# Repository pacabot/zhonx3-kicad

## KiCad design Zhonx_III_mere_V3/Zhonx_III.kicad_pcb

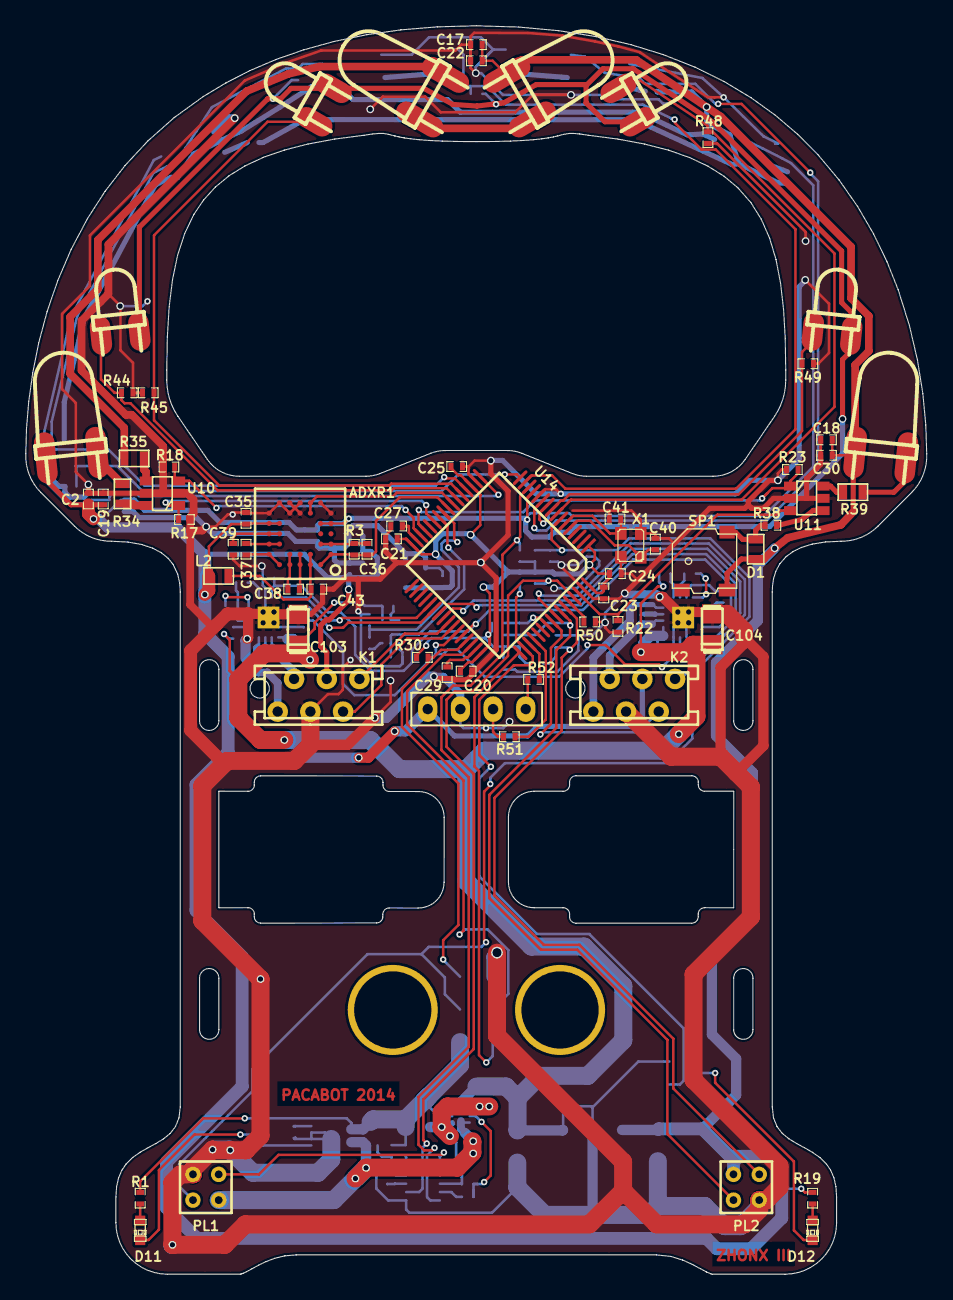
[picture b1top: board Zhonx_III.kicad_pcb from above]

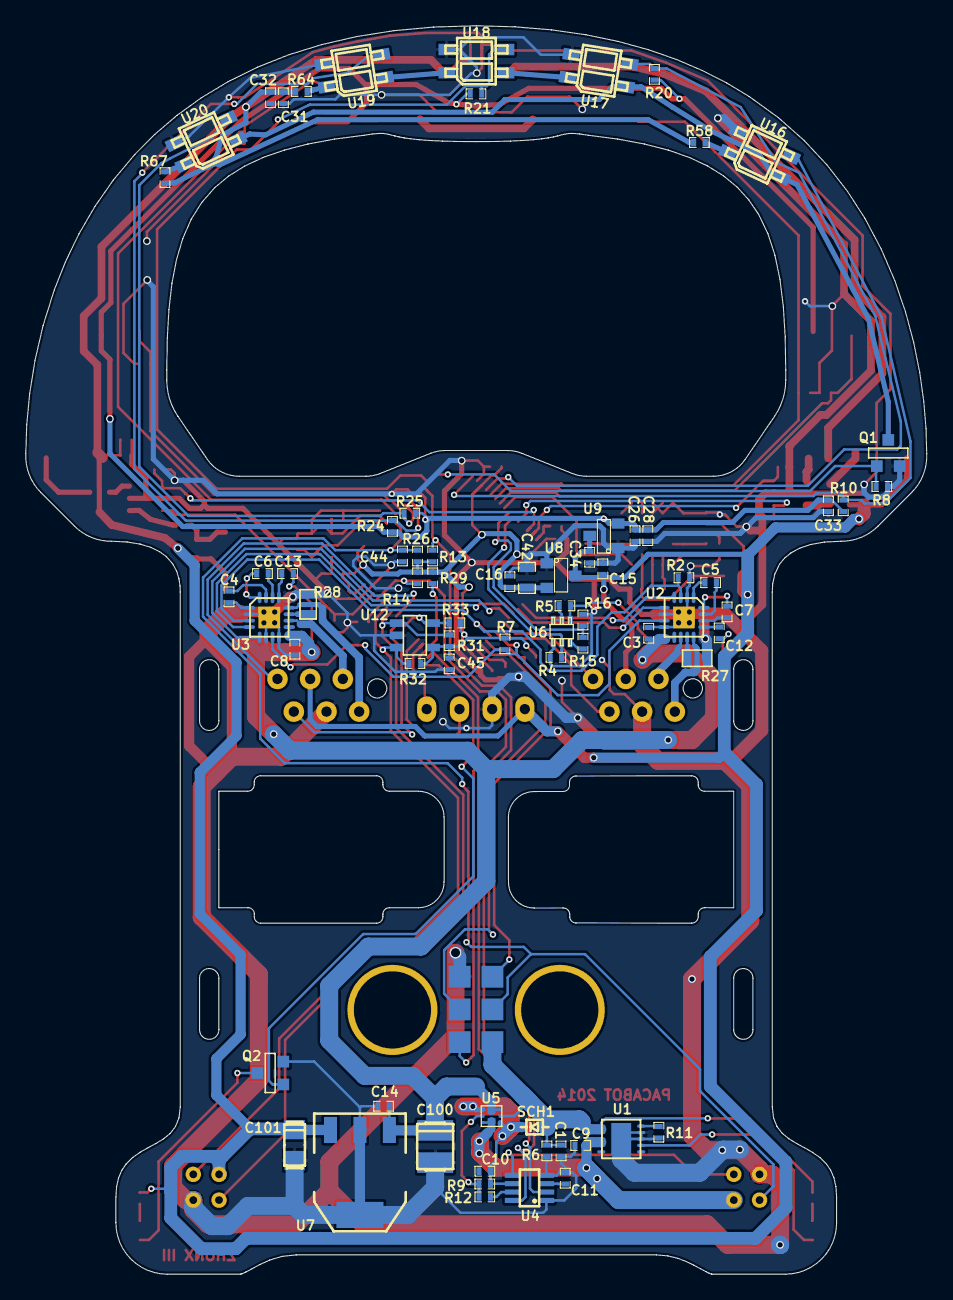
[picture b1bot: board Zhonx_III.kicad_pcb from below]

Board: 2 copper layers, 70.0 x 97.0 mm, 133 parts (73 on the bottom side), 104 nets.

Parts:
ADXR1: ADXRS620
C1, C9, C27, C29: 2,2uF; SM0402_ZHONX
C2, C17, C18, C20, C31: 4,7uF; SM0402_ZHONX
C3, C4, C5, C6, C7, C8, C10, C12, C13, C14, C15, C16, C19, C21, C22, C23, C24, C25, C30, C32, C33, C35, C39, C43, C44, C45: 0,1uF; SM0402_ZHONX
C11: 150nF; SM0402_ZHONX
C26, C34: 1uF; SM0402_ZHONX
C28: 10nF; SM0402_ZHONX
C36, C37, C38: 22nF; SM0402_ZHONX
C40, C41: 18pF; SM0402_ZHONX
C42: 10uF; SM0603_Capa
C100: 100uF; SM1210_Capa
C101, C103, C104: 100uF; SM1206_Capa
D1: 4148; SM0603
D11: Bleue; LED-0603
D12: Blanc; LED-0603
IR1: L_Front; IR_LF
IR2: L_Diag; IR_LD
IR3: R_Diag; IR_RD
IR4: R_Front; IR_RF
K1: L_Motor; Connecteur_Moteur_Zhonx
K2: R_Motor; Connecteur_Moteur_Zhonx
K3: USART; Conn_Serial_Zhonx
L2: 10uH; SM0603
P1: JTAG; Zhonx_III_JTAG
PL1: PLATINE_ZHONX_III; Platine_Zhonx_III
Q1, Q2: FDV301N; SOT23GDS
R1: 3,3K; SM0402_ZHONX
R2, R7, R8, R10, R13, R14, R17, R18, R20, R21, R22, R23, R24, R25, R29, R30, R33: 47K; SM0402_ZHONX
R3: 90K; SM0402_ZHONX
R4, R5: 1M; SM0402_ZHONX
R6, R9, R12, R26, R50: 100K; SM0402_ZHONX
R11, R16: 10K; SM0402_ZHONX
R15: 20K; SM0402_ZHONX
R19: 820; SM0402_ZHONX
R27, R28: 0,2; SM0603_ZHONX
R31, R32: 4,7K; SM0402_ZHONX
R34, R39: 12; SM0603_ZHONX
R35: 2,8; SM0603_ZHONX
R38: 100; SM0402_ZHONX
R44, R45, R48, R49: 1,8K; SM0402_ZHONX
R51, R52: 510; SM0402_ZHONX
R58, R67: 220; SM0402_ZHONX
R64: 33; SM0402_ZHONX
SCH1: BAT60; SOD323
SP1: KSSG13J12; Buzzer_KSSG13J12
U1: MCP73213
U2, U3: A3918; QFN16_Termal_Pad
U4: LTC2955CTS8-2; LTC2955
U5: SIB911DK; SC75-6L
U6: SI1551DL; SC70
U7: LM2940; SOT223
U8, U9: MCP1700; SOT23
U10, U11: BSL214N; SOT23_6
U12: 24LC64T; SOT23-5
U14: STM32F405RGT6; TQFP_64
U16: Line_1; QRE1113GR
U17: Line_2; QRE1113GR
U18: Line_3; QRE1113GR
U19: Line_4; QRE1113GR
U20: Line_5; QRE1113GR
X1: 16MHz; Quartz_8Z-16MHz

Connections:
+3.3V: C16.1, C20.2, C21.2, C23.2, C24.2, C25.2, C42.1, C45.1, R7.1, R13.2, R14.2, R26.1, R29.2, R30.1, R31.2, R32.2, R33.2, U8.2, U12.4, U14.1, U14.19, U14.32, U14.48, U14.64
+3.3VADC: ADXR1.1E, ADXR1.2E, C26.1, C28.1, C33.1, IR1.4, IR2.4, IR3.4, IR4.4, R10.1, R20.1, R21.1, R24.1, R25.1, U9.2, U14.13
+5V: ADXR1.6E, ADXR1.7E, C2.1, C15.1, C17.2, C18.1, C19.1, C22.2, C30.1, C31.1, C32.1, C34.1, C35.2, C101.1, D1.2, IR1.1, IR3.1, IR4.1, K1.4, K2.4, K3.4, L2.1, PL1.5, R19.2, R58.2, R64.2, R67.2, SP1.1, U7.3, U8.3, U9.3
+5VA: ADXR1.3A, ADXR1.3B, C43.1, L2.2
+8V: C3.2, C8.2, C12.1, C13.1, C14.1, C100.1, C103.1, C104.1, R5.1, U2.9, U3.9, U5.6, U6.4, U7.1
+9V: C1.1, P1.6, R1.2, R6.1, SCH1.1, U1.1, U1.2, U5.5
+BATT: C9.1, PL1.4, U1.3, U1.4, U5.3
Diag_TX: R18.1, U10.3, U14.30
Enable_IR_Line: Q1.G, R8.1, U14.16
FL: R7.2, U2.7, U3.7, U14.43
GET_BAT_ADC: R4.2, U6.2, U14.26
GND: ADXR1.1F, ADXR1.2G, ADXR1.4F, ADXR1.4G, ADXR1.5F, ADXR1.5G, ADXR1.6G, ADXR1.7F, C1.2, C2.2, C3.1, C8.1, C9.2, C10.1, C11.2, C14.2, C15.2, C16.2, C17.1, C18.2, C19.2, C20.1, C21.1, C22.1, C23.1, C24.1, C25.1, C26.2, C27.1, C28.2, C29.1, C30.2, C31.2, C32.2, C33.2, C34.2, C35.1, C39.2, C40.2, C41.2, C42.2, C43.2, C44.1, C45.2, C100.2, C101.2, C103.2, C104.2, K1.3, K2.3, K3.3, P1.1, PL1.1, PL1.8, Q1.S, Q2.S, R2.1, R4.1, R6.2, R8.2, R11.1, R16.1, R17.2, R18.2, R22.2, R23.2, R27.2, R28.2, R44.1, R45.2, R48.2, R49.2, R50.1, U1.8, U1.9, U2.2, U2.6, U2.8, U2.17, U3.2, U3.6, U3.8, U3.17, U4.1, U4.4, U6.1, U7.2, U7.4, U8.1, U9.1, U10.2, U10.5, U11.2, U11.5, U12.2, U14.12, U14.18, U14.63, U16.4, U17.4, U18.4, U19.4, U20.4, X1.2, X1.4
GPIO_BASE: P1.2, R30.2, U14.45
GYRO_RATE: ADXR1.1B, ADXR1.2A, C36.1, R3.2, U14.24
GYRO_TEMP: ADXR1.3F, ADXR1.3G, U14.23
I2C_SCL: PL1.7, R31.1, U12.1, U14.58
I2C_SDA: PL1.6, R32.1, U12.3, U14.59
LDiag_RX: IR2.3, R45.1, U14.21
LFront_RX: IR1.3, R44.2, U14.22
LFront_TX: R17.1, U10.1, U14.27
L_ENC_A: K1.6, U14.41
L_ENC_B: K1.5, U14.42
L_IN1: U2.4, U14.37
L_IN2: U2.5, U14.38
Line_IR_F: R21.2, U14.15, U18.3
Line_IR_L1: R20.2, U14.20, U17.3
Line_IR_L2: R10.2, U14.17, U16.3
Line_IR_R1: R24.2, U14.11, U19.3
Line_IR_R2: R25.2, U14.10, U20.3
unnamed: U18.1, U19.2
unnamed: C29.2, U14.47
unnamed: C10.2, R9.1, SCH1.2, U4.6, U5.1, U5.4
unnamed: R9.2, R12.1, U5.2
unnamed: K3.2, R51.2
unnamed: K3.1, R52.2
unnamed: U17.1, U18.2
unnamed: R12.2, U4.7
unnamed: D11.2, U1.7
unnamed: C27.2, U14.31
unnamed: C40.1, U14.5, X1.3
unnamed: R50.2, U14.60
unnamed: K2.2, U3.10
unnamed: K2.1, U3.12
unnamed: C4.2, U3.1
unnamed: R28.1, U3.11
unnamed: C6.1, U3.16
unnamed: C13.2, U3.13
unnamed: K1.1, U2.12
unnamed: K1.2, U2.10
unnamed: C12.2, U2.13
unnamed: C5.2, U2.1
unnamed: D12.2, Q2.D
unnamed: R27.1, U2.11
unnamed: C7.1, U2.16
unnamed: C5.1, U2.15
unnamed: C7.2, U2.14
unnamed: ADXR1.6D, ADXR1.7D, C39.1
unnamed: R5.2, U6.5, U6.6
unnamed: ADXR1.1C, ADXR1.2C, C36.2, R3.1
unnamed: C6.2, U3.14
unnamed: ADXR1.6A, ADXR1.7B, C37.1
unnamed: C4.1, U3.15
unnamed: IR2.1, IR3.2
unnamed: Q1.D, U16.2, U17.2, U20.2
unnamed: IR4.2, R39.1
unnamed: IR2.2, R35.2
unnamed: C41.1, U14.6, X1.1
unnamed: IR1.2, R34.1
unnamed: ADXR1.4A, ADXR1.4B, C38.1
unnamed: ADXR1.5A, ADXR1.5B, C38.2
unnamed: ADXR1.6C, ADXR1.7C, C37.2
unnamed: D1.1, R38.1, SP1.2
unnamed: R58.1, U16.1
unnamed: R64.1, U19.1
unnamed: R67.1, U20.1
unnamed: R15.2, U6.3
unnamed: D12.1, R19.1
unnamed: C11.1, U4.3
unnamed: D11.1, R1.1
unnamed: R35.1, U10.4
unnamed: R39.2, U11.6
unnamed: R38.2, U11.4
unnamed: R34.2, U10.6
unnamed: R11.2, U1.10
NSRST: C44.2, P1.4, PL1.3, R26.2, U14.7
ON/OFF: PL1.2, U4.5
PA13/JTMS-SWDAT: P1.3, U14.46
PA14/JTCK-SWCLK: P1.5, U14.49
PIEZZO: R22.1, U11.3, U14.62
POWER_KILL: R14.1, U4.2, U14.61
PW_LED: Q2.G, R29.1, U14.50
RDiag_RX: IR3.3, R48.1, U14.8
RFront_RX: IR4.3, R49.1, U14.9
RFront_TX: R23.1, U11.1, U14.29
R_ENC_A: K2.5, U14.56
R_ENC_B: K2.6, U14.57
R_IN1: U3.4, U14.39
R_IN2: U3.5, U14.40
SLEEP: R2.2, U2.3, U3.3, U14.44
TEST_BAT: R15.1, R16.2, U14.25
USART_RX: R51.1, U14.52
USART_TX: R52.1, U14.51
WKUP: R13.1, U4.8, U14.14
WP_EEPROM: R33.1, U12.5, U14.55

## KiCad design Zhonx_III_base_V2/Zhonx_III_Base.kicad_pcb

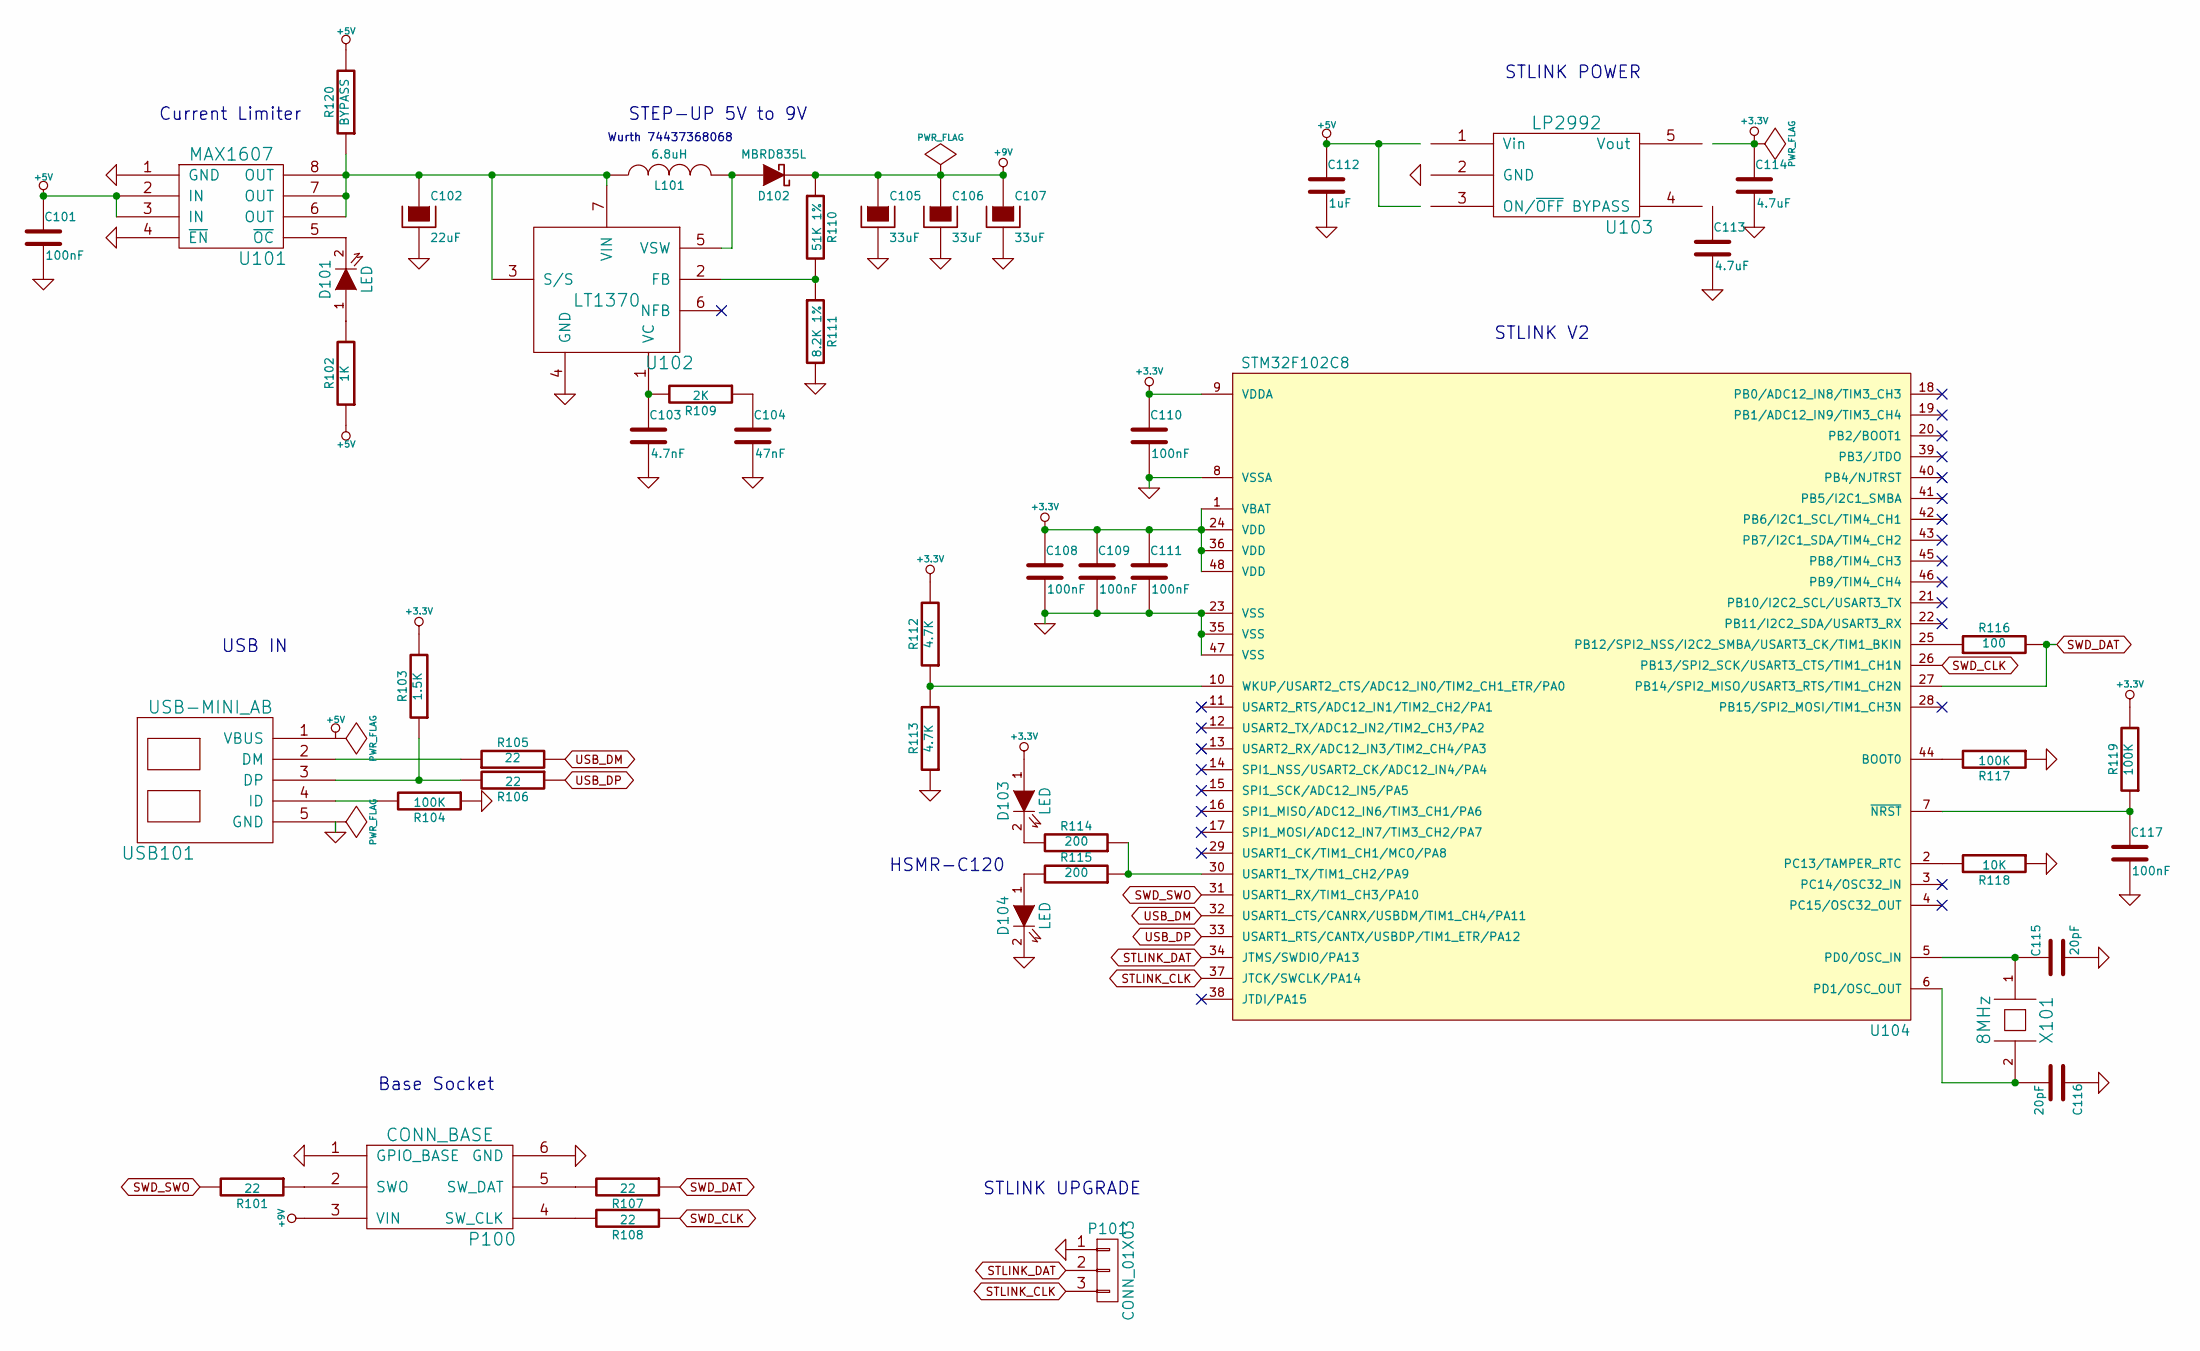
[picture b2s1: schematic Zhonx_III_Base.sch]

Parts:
C101, C108, C109, C110, C111, C117: 100nF; C_0603
C102: 22uF; C_1812
C103: 4.7nF; C_0603
C104: 47nF; C_0603
C105, C106, C107: 33uF; C_1812
C112: 1uF; C_0603
C113, C114: 4.7uF; C_0805
C115, C116: 20pF; C_0603
D101, D103, D104: LED; LED_HMSx-C120
D102: MBRD835L; DPAK_2
L101: 6.8uH; WURTH_INDUCTOR_1040
P100: CONN_BASE
P101: CONN_01X03; GS3
R101, R105, R106, R107, R108: 22; R_0603
R102: 1K; R_0603
R103: 1.5K; R_0603
R104, R117, R119: 100K; R_0603
R109: 2K; R_0603
R110: 51K 1%; R_0603
R111: 8.2K 1%; R_0603
R112, R113: 4.7K; R_0603
R114, R115: 200; R_0603
R116: 100; R_0603
R118: 10K; R_0603
R120: BYPASS; GS2
U101: MAX1607; SO-8
U102: LT1370; DD_PAK_7
U103: LP2992; SOT23-5
U104: STM32F102C8; LQFP-48_7x7mm_Pitch0.5mm
USB101: USB-MINI_AB; USB_MINI_AB
X101: 8MHz; Q_5x3.2

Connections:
+3.3V: C108.1, C109.1, C110.1, C111.1, C114.1, D103.1 (A), R103.2, R112.2, R119.2, U103.5 (Vout), U104.1 (VBAT), U104.9 (VDDA), U104.24 (VDD), U104.36 (VDD), U104.48 (VDD)
+5V: C101.1, C112.1, R102.1, R120.2, U101.2 (IN), U101.3 (IN), U103.1 (Vin), U103.3 (ON/~OFF), USB101.1 (VBUS)
+9V: C105.1, C106.1, C107.1, D102.2 (K), P100.3 (VIN), R110.1
GND: C101.2, C102.2, C103.2, C104.2, C105.2, C106.2, C107.2, C108.2, C109.2, C110.2, C111.2, C112.2, C113.2, C114.2, C115.2, C116.1, C117.2, D104.2 (K), P100.1 (GPIO_BASE), P100.6 (GND), P101.1, R104.1, R111.2, R113.1, R117.1, R118.1, U101.1 (GND), U101.4 (~EN), U102.4 (GND), U103.2 (GND), U104.8 (VSSA), U104.23 (VSS), U104.35 (VSS), U104.47 (VSS), USB101.5 (GND)
unnamed: C102.1, L101.1, R120.1, U101.6 (OUT), U101.7 (OUT), U101.8 (OUT), U102.3 (S/S), U102.7 (VIN)
unnamed: C103.1, R109.2, U102.1 (VC)
unnamed: C104.1, R109.1
unnamed: C113.1, U103.4 (BYPASS)
unnamed: C115.1, U104.5 (PD0/OSC_IN), X101.1
unnamed: C116.2, U104.6 (PD1/OSC_OUT), X101.2
unnamed: C117.1, R119.1, U104.7 (~NRST)
unnamed: D101.1 (A), R102.2
unnamed: D101.2 (K), U101.5 (~OC)
unnamed: D102.1 (A), L101.2, U102.5 (VSW)
unnamed: D103.2 (K), R114.2
unnamed: D104.1 (A), R115.2
unnamed: P100.2 (SWO), R101.1
unnamed: P100.4 (SW_CLK), R108.2
unnamed: P100.5 (SW_DAT), R107.2
unnamed: R103.1, R106.2, USB101.3 (DP)
unnamed: R104.2, USB101.4 (ID)
unnamed: R105.1, USB101.2 (DM)
unnamed: R110.2, R111.1, U102.2 (FB)
unnamed: R112.1, R113.2, U104.10 (WKUP/USART2_CTS/ADC12_IN0/TIM2_CH1_ETR/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)
unnamed: R114.1, R115.1, U104.30 (USART1_TX/TIM1_CH2/PA9)
unnamed: R116.1, U104.25 (PB12/SPI2_NSS/I2C2_SMBA/USART3_CK/TIM1_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)
unnamed: R117.2, U104.44 (BOOT0)
unnamed: R118.2, U104.2 (PC13/TAMPER_RTC)
STLINK_CLK: P101.3, U104.37 (JTCK/SWCLK/PA14)
STLINK_DAT: P101.2, U104.34 (JTMS/SWDIO/PA13)
SWD_CLK: R108.1, U104.26 (PB13/SPI2_SCK/USART3_CTS/TIM1_CH1N)
SWD_DAT: R107.1, R116.2, U104.27 (PB14/SPI2_MISO/USART3_RTS/TIM1_CH2N)
SWD_SWO: R101.2, U104.31 (USART1_RX/TIM1_CH3/PA10)
USB_DM: R105.2, U104.32 (USART1_CTS/CANRX/USBDM/TIM1_CH4/PA11)
USB_DP: R106.1, U104.33 (USART1_RTS/CANTX/USBDP/TIM1_ETR/PA12)

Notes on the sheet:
STLINK UPGRADE
Base Socket
STEP-UP 5V to 9V
Current Limiter
USB IN
STLINK V2
STLINK POWER
Wurth 74437368068
HSMR-C120

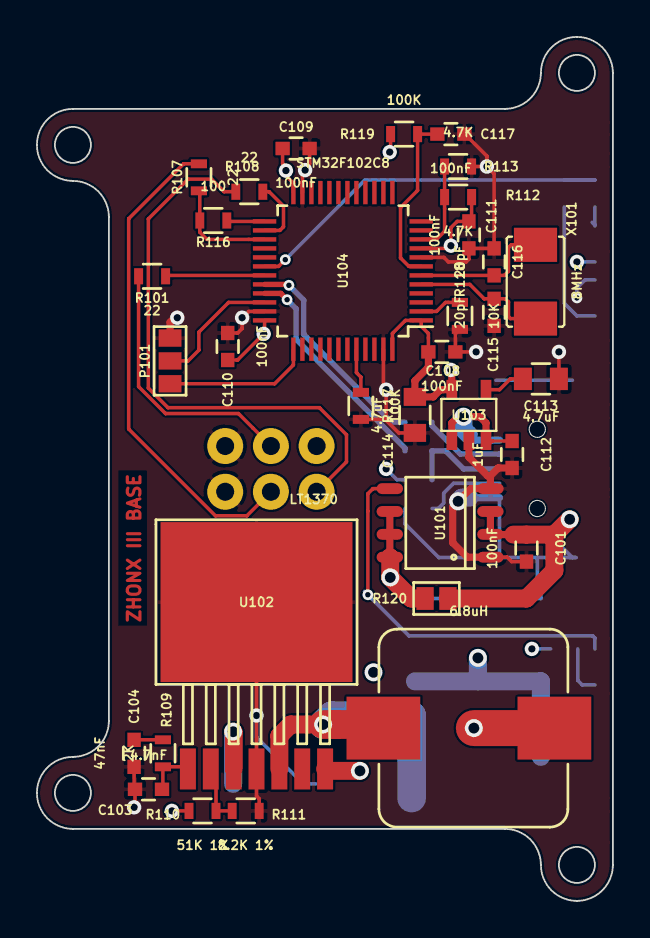
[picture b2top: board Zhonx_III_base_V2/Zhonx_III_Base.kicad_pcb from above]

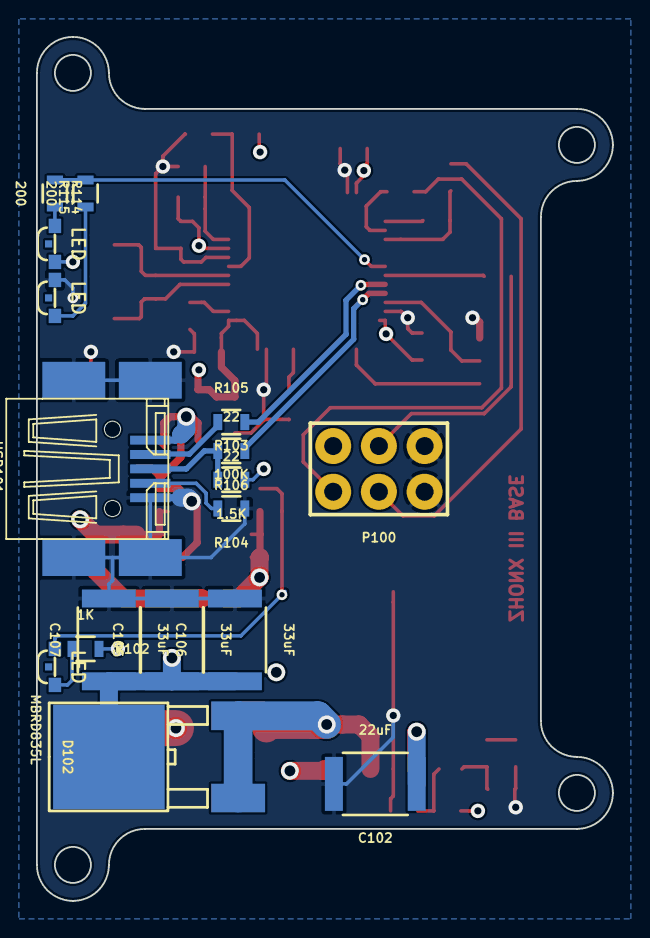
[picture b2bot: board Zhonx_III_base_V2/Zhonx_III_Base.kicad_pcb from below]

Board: 4 copper layers, 32.0 x 48.0 mm, 50 parts (17 on the bottom side), 35 nets.

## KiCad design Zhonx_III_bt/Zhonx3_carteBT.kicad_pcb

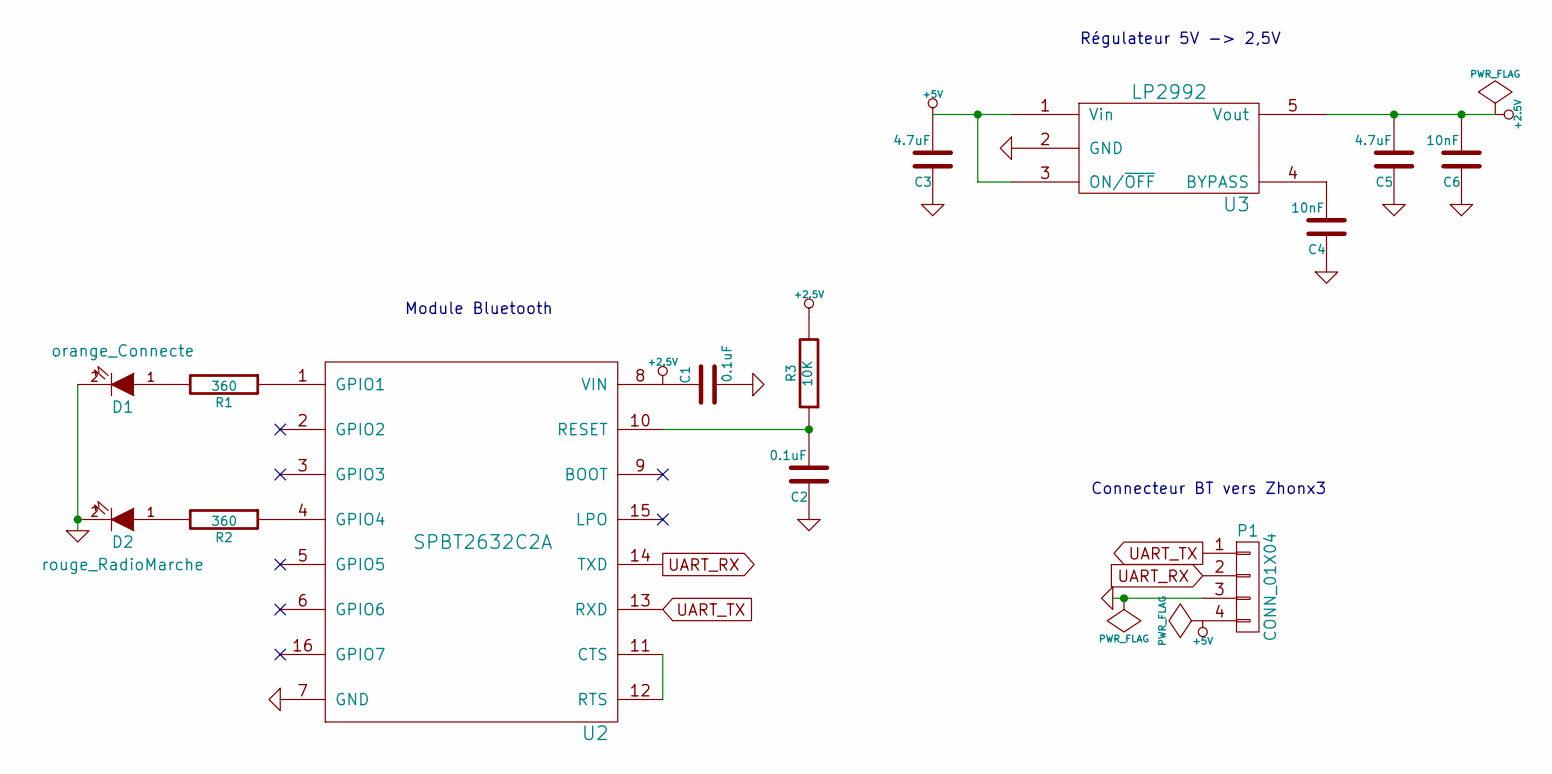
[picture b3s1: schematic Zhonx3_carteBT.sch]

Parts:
C1, C2: 0.1uF; SMD-0402_c
C3, C5: 4.7uF; SMD-0402_c
C4, C6: 10nF; SMD-0402_c
D1: orange_Connecte; LED-0603
D2: rouge_RadioMarche; LED-0603
P1: CONN_01X04; Socket_Strip_Straight_1x04
R1, R2: 360; SMD-0402_r
R3: 10K; SMD-0402_r
U2: SPBT2632C2A
U3: LP2992; SOT-23-5

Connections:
+2.5V: C1.1, C5.2, C6.2, R3.2, U2.8 (VIN), U3.5 (Vout)
+5V: C3.2, P1.4, U3.1 (Vin), U3.3 (ON/~OFF)
GND: C1.2, C2.1, C3.1, C4.1, C5.1, C6.1, D1.2 (K), D2.2 (K), P1.3, U2.7 (GND), U3.2 (GND)
unnamed: C2.2, R3.1, U2.10 (RESET)
unnamed: C4.2, U3.4 (BYPASS)
unnamed: D1.1 (A), R1.2
unnamed: D2.1 (A), R2.2
unnamed: R1.1, U2.1 (GPIO1)
unnamed: R2.1, U2.4 (GPIO4)
unnamed: U2.11 (CTS), U2.12 (RTS)
UART_RX: P1.2, U2.14 (TXD)
UART_TX: P1.1, U2.13 (RXD)

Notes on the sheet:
Connecteur BT vers Zhonx3
Régulateur 5V -> 2,5V
Module Bluetooth

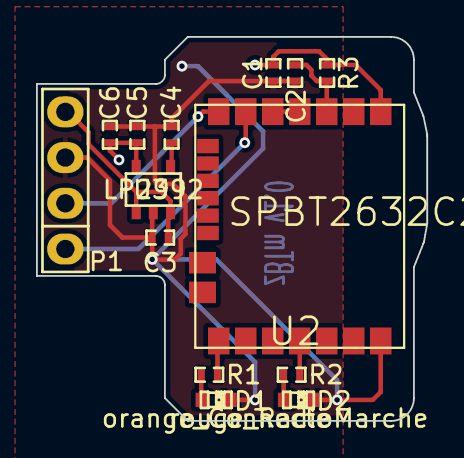
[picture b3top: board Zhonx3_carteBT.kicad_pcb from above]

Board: 4 copper layers, 21.7 x 21.3 mm, 14 parts (0 on the bottom side), 12 nets.

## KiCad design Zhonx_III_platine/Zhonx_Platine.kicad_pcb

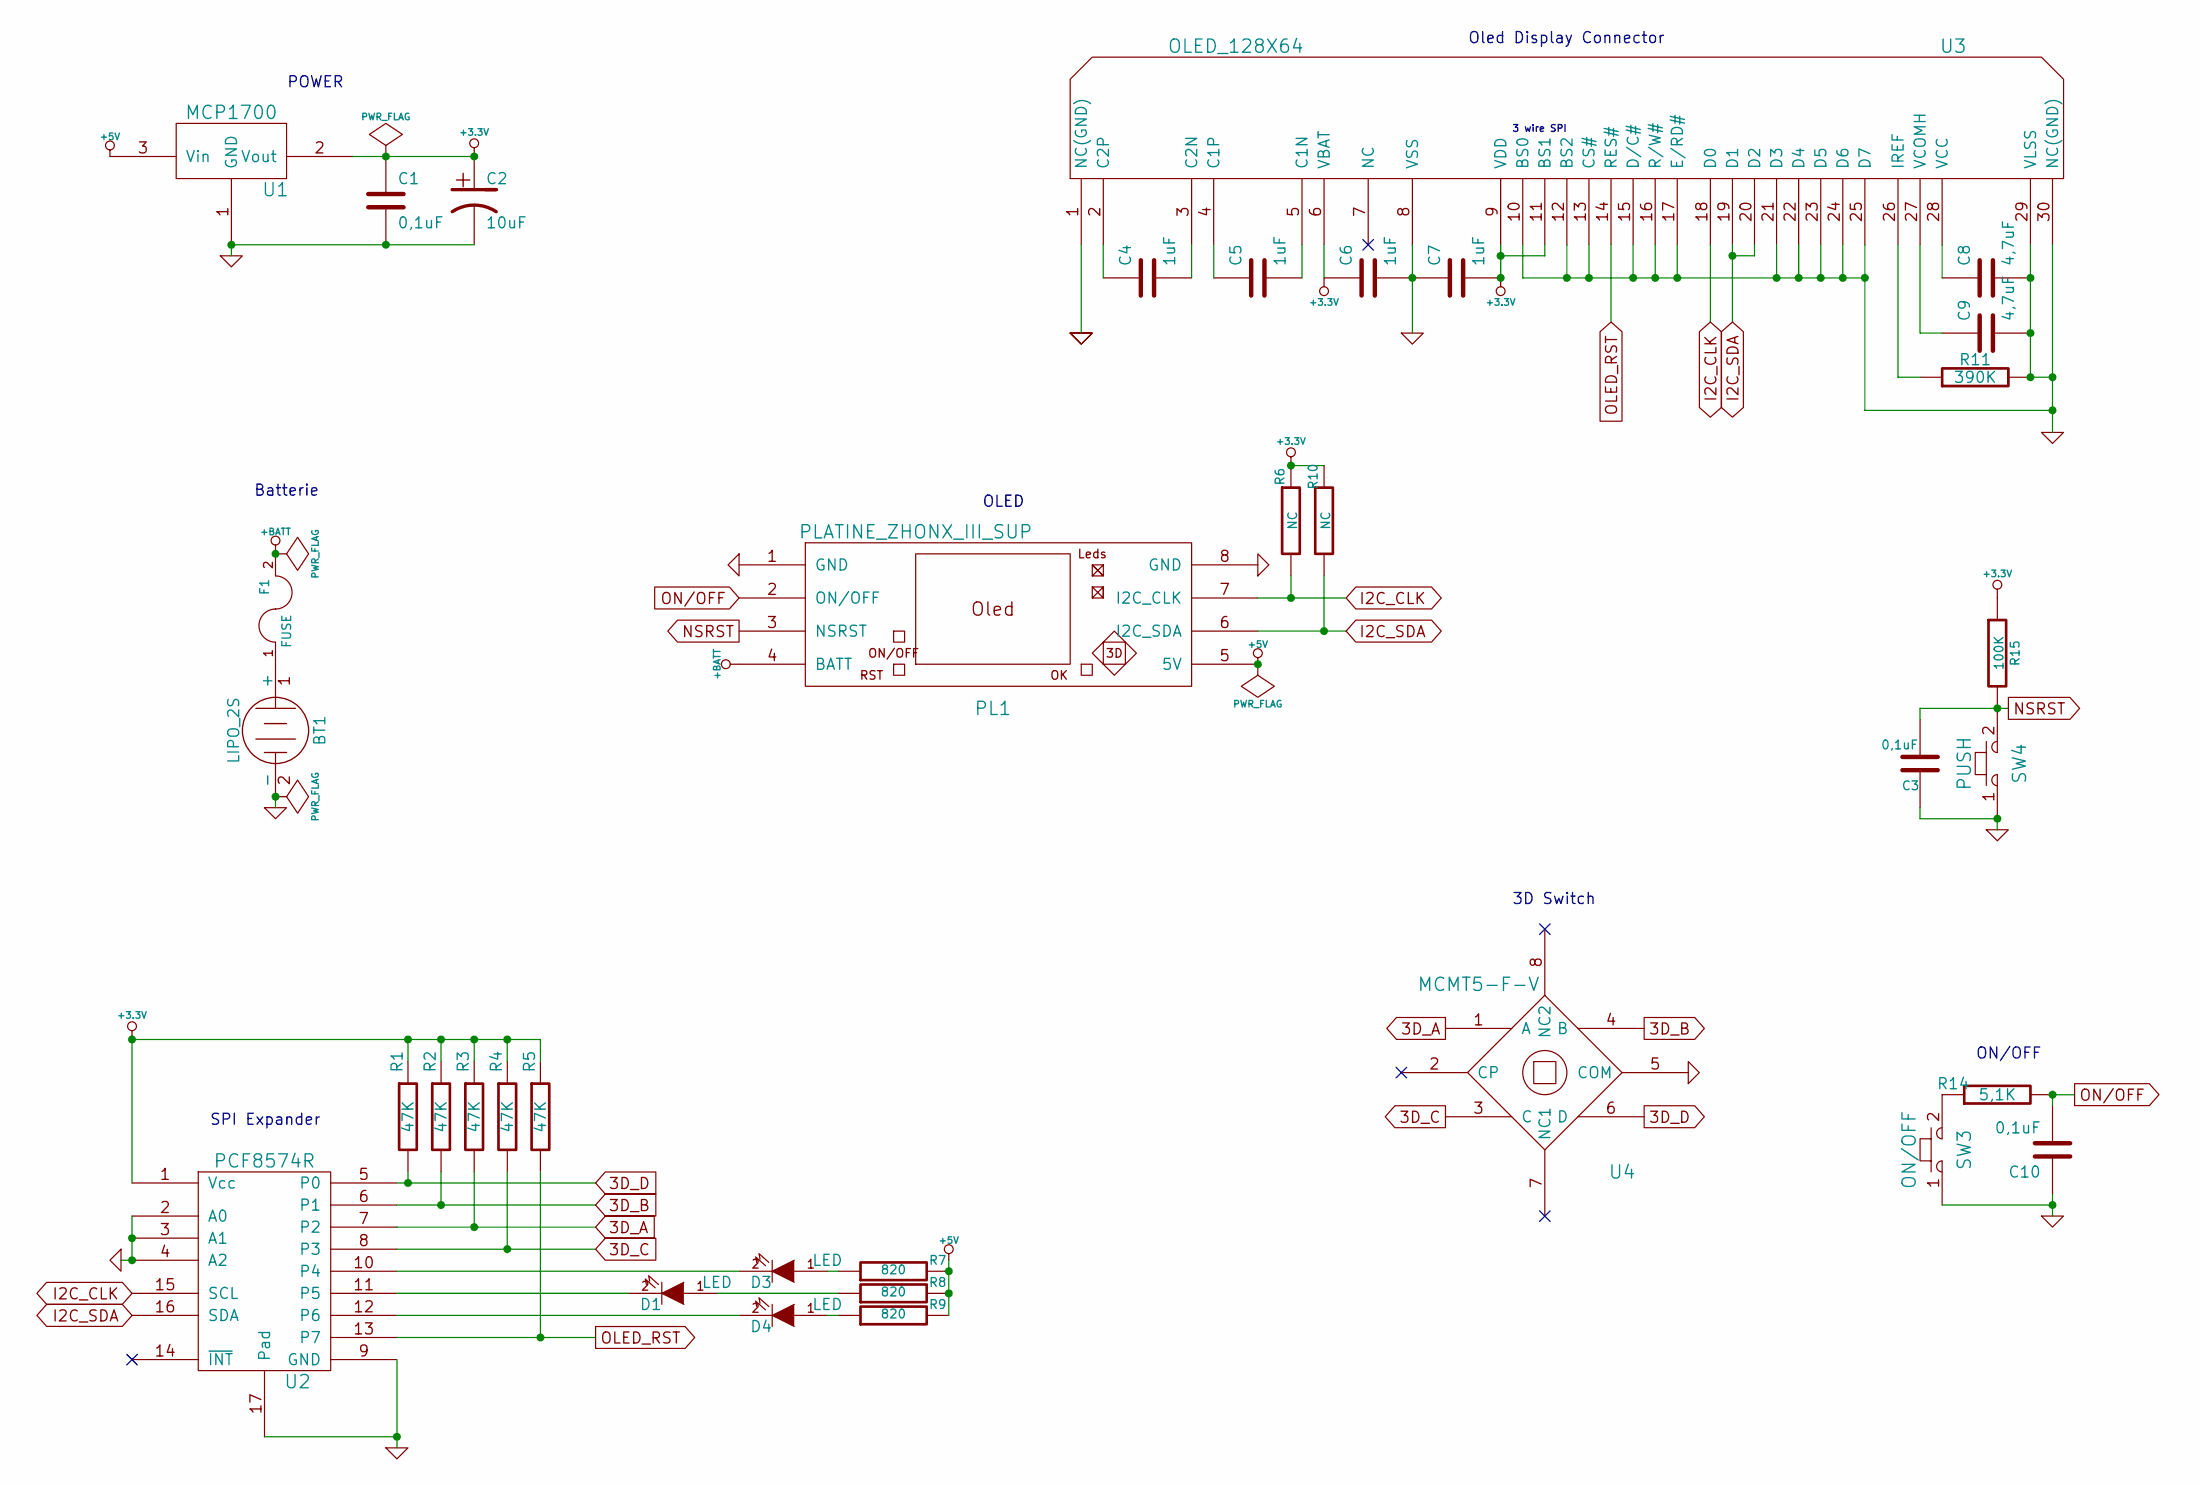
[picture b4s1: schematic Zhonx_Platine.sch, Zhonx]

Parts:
BT1: LIPO_2S
C1, C10: 0,1uF
C2: 10uF
C3: 0,1uF
C4, C5, C6, C7: 1uF
C8, C9: 4,7uF
D1, D3, D4: LED
F1: FUSE
PL1: PLATINE_ZHONX_III_SUP
R1, R2, R3, R4, R5: 47K
R6, R10: NC
R7, R8, R9: 820
R11: 390K
R14: 5,1K
R15: 100K
SW3: ON/OFF
SW4: PUSH
U1: MCP1700
U2: PCF8574R
U3: OLED_128X64
U4: MCMT5-F-V

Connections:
3D_A: R3.2, U2.7 (P2), U4.1 (A)
3D_B: R2.2, U2.6 (P1), U4.4 (B)
3D_C: R4.2, U2.8 (P3), U4.3 (C)
3D_D: R1.2, U2.5 (P0), U4.6 (D)
+3.3V: C1.1, C2.1, C6.1, C7.2, R1.1, R2.1, R3.1, R4.1, R5.1, R6.1, R10.1, R15.1, U1.2 (Vout), U2.1 (Vcc), U3.6 (VBAT), U3.9 (VDD), U3.11 (BS1)
+5V: PL1.5 (5V), R7.2, R8.2, R9.2, U1.3 (Vin)
+BATT: F1.2, PL1.4 (BATT)
GND: BT1.2 (-), C1.2, C2.2, C3.1, C6.2, C7.1, C8.2, C9.2, C10.1, PL1.1 (GND), PL1.8 (GND), R11.2, SW3.1, SW4.1, U1.1 (GND), U2.2 (A0), U2.3 (A1), U2.4 (A2), U2.9 (GND), U2.17 (Pad), U3.1 (NC(GND)), U3.8 (VSS), U3.10 (BS0), U3.12 (BS2), U3.13 (CS#), U3.15 (D/C#), U3.16 (R/W#), U3.17 (E/RD#), U3.21 (D3), U3.22 (D4), U3.23 (D5), U3.24 (D6), U3.25 (D7), U3.29 (VLSS), U3.30 (NC(GND)), U4.5 (COM)
I2C_CLK: PL1.7 (I2C_CLK), R6.2, U2.15 (SCL), U3.18 (D0)
I2C_SDA: PL1.6 (I2C_SDA), R10.2, U2.16 (SDA), U3.19 (D1), U3.20 (D2)
unnamed: D3.2 (K), U2.10 (P4)
unnamed: D1.2 (K), U2.11 (P5)
unnamed: D4.2 (K), U2.12 (P6)
unnamed: BT1.1 (+), F1.1
unnamed: D4.1 (A), R9.1
unnamed: D3.1 (A), R7.1
unnamed: D1.1 (A), R8.1
unnamed: R11.1, U3.26 (IREF)
unnamed: C5.2, U3.5 (C1N)
unnamed: C4.2, U3.3 (C2N)
unnamed: C9.1, U3.27 (VCOMH)
unnamed: C8.1, U3.28 (VCC)
unnamed: C4.1, U3.2 (C2P)
unnamed: C5.1, U3.4 (C1P)
unnamed: R14.1, SW3.2
NSRST: C3.2, PL1.3 (NSRST), R15.2, SW4.2
OLED_RST: R5.2, U2.13 (P7), U3.14 (RES#)
ON/OFF: C10.2, PL1.2 (ON/OFF), R14.2

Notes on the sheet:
SPI Expander
3D Switch
Oled Display Connector
3 wire SPI
ON/OFF
OLED
Batterie
POWER

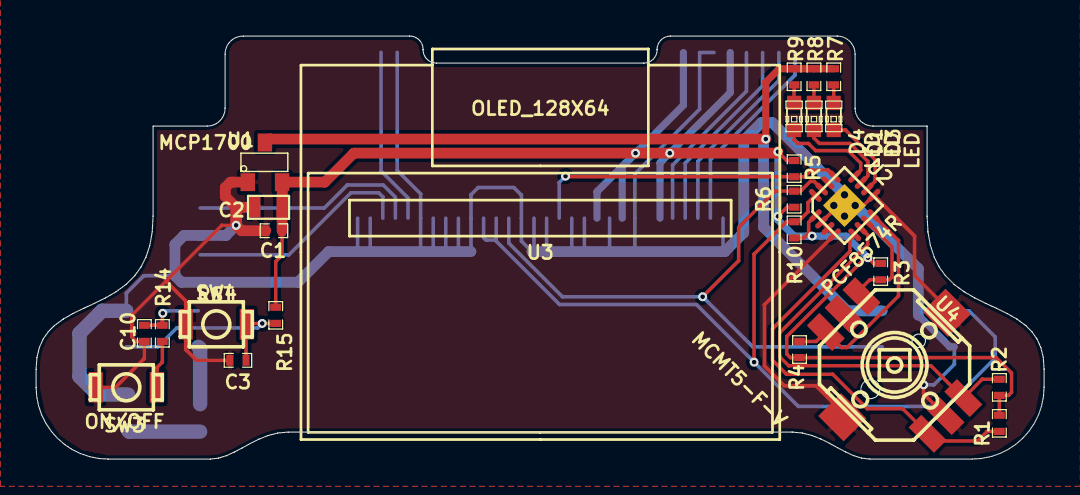
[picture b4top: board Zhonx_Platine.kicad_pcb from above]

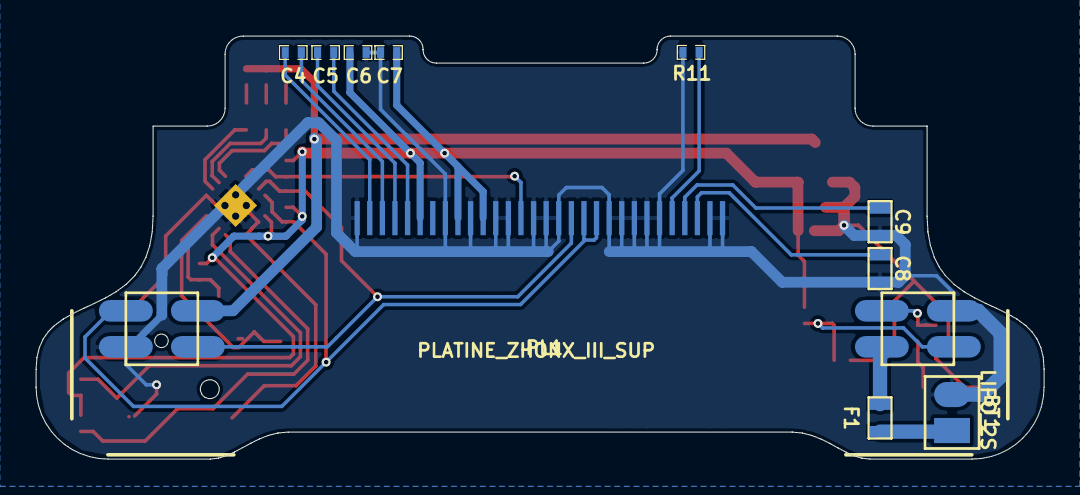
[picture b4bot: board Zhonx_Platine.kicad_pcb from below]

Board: 2 copper layers, 56.0 x 23.5 mm, 35 parts (10 on the bottom side), 28 nets.

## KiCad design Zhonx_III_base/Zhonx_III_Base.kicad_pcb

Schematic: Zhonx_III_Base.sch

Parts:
C1, C2, C5: 100nF
D1, D2: LED
JT1: JTAG_ZHONX
P1: CONN_BASE
R1: R
R2, R3: 1K
R4: 0
SW1: SW_PUSH
U1: MAX1607
U2: POLOLU_U3V50

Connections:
+5V: C1.1, JT1.5, JT1.6, R2.1, R3.1, U1.2 (IN), U1.3 (IN)
+9V: P1.3 (VIN), R4.2
/RST: C5.2, P1.2 (RST), R1.1, SW1.1
/SWD_CLK: JT1.8, P1.4 (SW_CLK)
/SWD_DAT: JT1.10, P1.5 (SW_DAT)
GND: C1.2, C2.2, C5.1, D1.2 (K), JT1.2, JT1.9, P1.1 (GPIO_BASE), P1.6 (GND), SW1.2, U1.1 (GND), U1.4 (~EN), U2.1 (GND), U2.3 (GND)
unnamed: D2.1 (A), R3.2
unnamed: R4.1, U2.4 (VOUT)
unnamed: D2.2 (K), U1.5 (~OC)
unnamed: D1.1 (A), R2.2
unnamed: JT1.1, R1.2
unnamed: C2.1, U1.6 (OUT), U1.7 (OUT), U1.8 (OUT), U2.2 (VIN)

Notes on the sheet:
JTAG STM32
Base Socket
STEP-UP 5V to 9V
Current Limiter

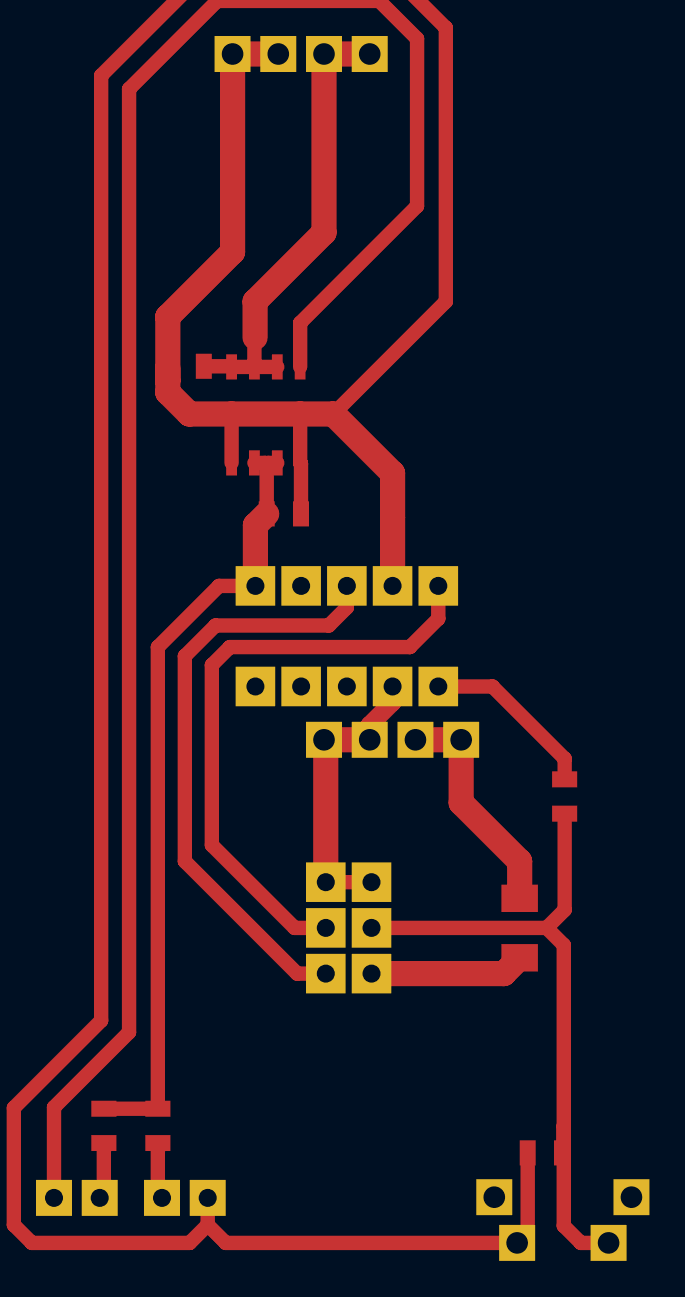
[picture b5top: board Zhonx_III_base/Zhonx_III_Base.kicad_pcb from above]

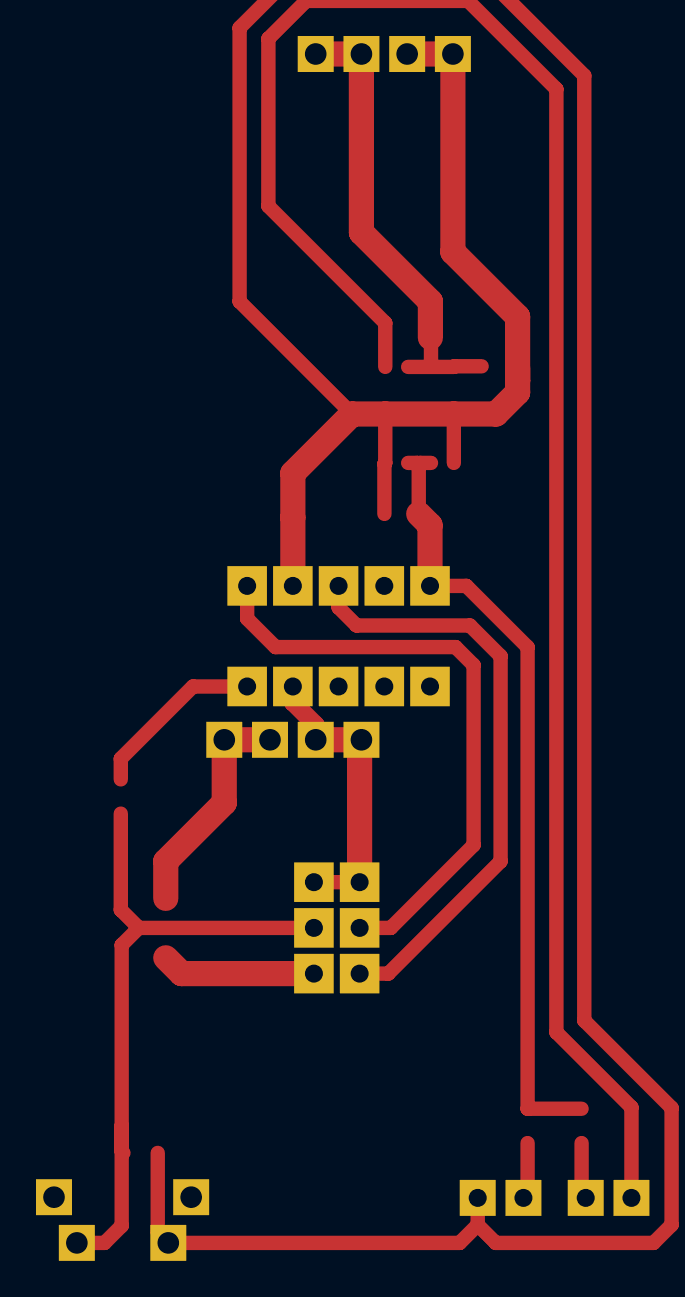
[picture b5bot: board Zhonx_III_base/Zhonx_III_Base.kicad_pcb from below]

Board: 2 copper layers, 14 parts (6 on the bottom side), 12 nets.

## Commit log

2015-01-23 ajout carte BT
2015-01-30 Ajout librairies Zhonx 3
2015-02-06 bluetooth passage en 4 couches
2015-02-06 add .gitignore
2015-02-06 Organisation des librairies
2015-02-06 Ajout Librairies
2015-02-06 add gitignore
2015-03-05 mise a jour schéma carte mère (mesure courant, 4 résistances encodeurs)
2015-03-05 Nouvelle librairie (.pretty)
2015-03-05 Suppréssion Kicad_Lib
2015-03-05 modification affectations E/S STM32
2015-03-09 Create Zhonx mere V2
2015-03-09 Update Base V2
2015-03-20 Add ZHONX_III V2
2015-05-01 routage pcb (debut ...)
2015-05-01 Update Base_V2 (CamBam DXF)
2015-05-01 Add CamBam DXF for Base_V2
2015-05-01 Update .gitignore (*-bak)
2016-12-10 Update schematic libs
2016-12-10 add rescue lib
2016-12-10 add Classeur.xlsx
2016-12-10 repair mod librairies
2017-01-27 add main lib
2017-01-27 Rename and move libs
2017-01-27 add main_lib
2017-01-27 rename libs
2017-01-27 add new libs
2017-01-27 update lib settigns
2017-01-27 new V3 version
